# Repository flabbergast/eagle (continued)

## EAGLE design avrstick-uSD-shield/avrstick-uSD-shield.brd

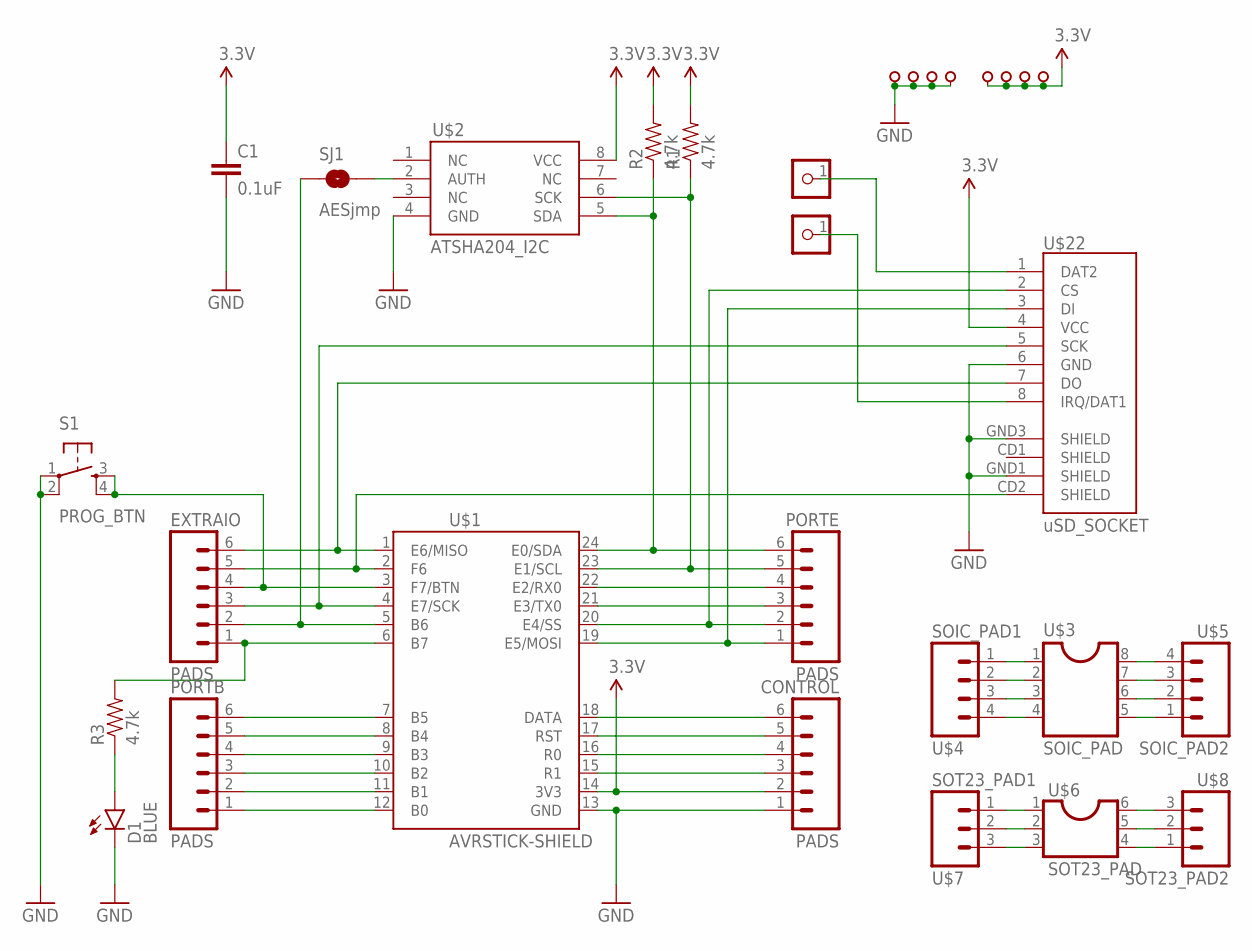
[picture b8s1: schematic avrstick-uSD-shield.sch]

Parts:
C1: 0.1uF; 1206
CONTROL: PADS; M06_SIDESILK_B
D1: BLUE; LED-1206
EXTRAIO: PADS; M06_SIDESILK_T
J1, J2: CON_HEADER_1X01-SMD; SMDPAD05X05
PORTB: PADS; M06_SIDESILK_T
PORTE: PADS; M06_SIDESILK_B
R1, R2, R3: 4.7k; 1206
S1: PROG_BTN; TACTILE-SWITCH-SMD
SJ1: AESjmp; PAD-JUMPER-2-NO_YES_SILK
U$1: AVRSTICK-SHIELD
U$2: ATSHA204_I2C; SOIC-8-NARROW
U$3: SOIC_PAD; SOIC-8-NARROW
U$4: SOIC_PAD1; M04_SILK_1SQ
U$5: SOIC_PAD2; M04_SILK
U$6: SOT23_PAD; SOT23-6
U$7: SOT23_PAD1; M03_SILK_1SQ
U$8: SOT23_PAD2; M03_SILK
U$9, U$10, U$11, U$12, U$13, U$14: M01_SIDESILK
U$15, U$16: M01_NOSILK
U$22: uSD_SOCKET; MICROSD_SOCKET_SPARKFUN

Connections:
3.3V: C1.1, CONTROL.2, R1.2, R2.2, U$1.14 (3V3), U$2.8 (VCC), U$12.1, U$13.1, U$14.1, U$16.1, U$22.4 (VCC)
GND: C1.2, CONTROL.1, D1.C, S1.1, S1.2, U$1.13 (GND), U$2.4 (GND), U$9.1, U$10.1, U$11.1, U$15.1, U$22.6 (GND), U$22.GND1 (SHIELD), U$22.GND3 (SHIELD)
unnamed: EXTRAIO.1, R3.2, U$1.6 (B7)
unnamed: EXTRAIO.2, SJ1.1, U$1.5 (B6)
unnamed: EXTRAIO.3, U$1.4 (E7/SCK), U$22.5 (SCK)
unnamed: PORTB.6, U$1.7 (B5)
unnamed: EXTRAIO.5, U$1.2 (F6), U$22.CD2 (SHIELD)
unnamed: EXTRAIO.6, U$1.1 (E6/MISO), U$22.7 (DO)
unnamed: EXTRAIO.4, S1.3, S1.4, U$1.3 (F7/BTN)
unnamed: PORTB.5, U$1.8 (B4)
unnamed: PORTB.4, U$1.9 (B3)
unnamed: PORTB.3, U$1.10 (B2)
unnamed: PORTB.2, U$1.11 (B1)
unnamed: PORTB.1, U$1.12 (B0)
unnamed: SJ1.2, U$2.2 (AUTH)
unnamed: D1.A, R3.1
unnamed: CONTROL.3, U$1.15 (R1)
unnamed: CONTROL.4, U$1.16 (R0)
unnamed: CONTROL.5, U$1.17 (RST)
unnamed: CONTROL.6, U$1.18 (DATA)
unnamed: PORTE.1, U$1.19 (E5/MOSI), U$22.3 (DI)
unnamed: PORTE.2, U$1.20 (E4/SS), U$22.2 (CS)
unnamed: PORTE.3, U$1.21 (E3/TX0)
unnamed: PORTE.4, U$1.22 (E2/RX0)
unnamed: PORTE.5, R1.1, U$1.23 (E1/SCL), U$2.6 (SCK)
unnamed: PORTE.6, R2.1, U$1.24 (E0/SDA), U$2.5 (SDA)
unnamed: U$3.5, U$5.1
unnamed: U$3.6, U$5.2
unnamed: U$3.7, U$5.3
unnamed: U$3.8, U$5.4
unnamed: U$3.1, U$4.1
unnamed: U$3.2, U$4.2
unnamed: U$3.3, U$4.3
unnamed: U$3.4, U$4.4
unnamed: U$6.4, U$8.1
unnamed: U$6.5, U$8.2
unnamed: U$6.6, U$8.3
unnamed: U$6.1, U$7.1
unnamed: U$6.2, U$7.2
unnamed: U$6.3, U$7.3
unnamed: J2.1, U$22.8 (IRQ/DAT1)
unnamed: J1.1, U$22.1 (DAT2)

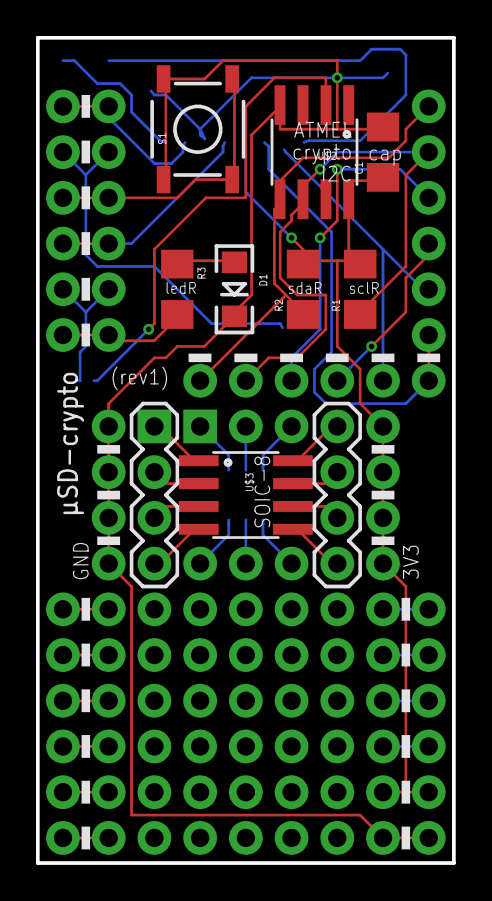
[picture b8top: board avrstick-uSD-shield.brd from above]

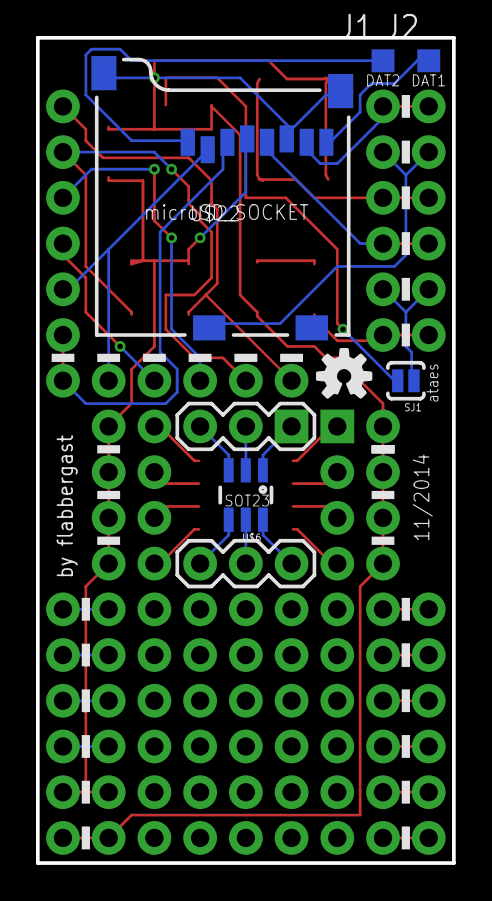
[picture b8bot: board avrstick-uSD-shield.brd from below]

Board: 2 copper layers, 23.1 x 45.8 mm, 36 parts (8 on the bottom side), 42 nets.

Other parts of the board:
U$17, U$18, U$19, U$20, U$21: M06_PROTOPAD; M06_NOSILK
U$23: OSHW-LOGO-S

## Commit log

2014-12-11 Add avrstick-uSD-shield and uext-microSD.
2014-12-17 Add X-A4U rev1 stick.
2015-02-09 Add X-A4U-r2.
2015-02-10 Add png schematic of X-A4U-r2 board.
2015-03-18 Update silk on X-A4U-r2 (2.1).
2015-05-16 Add little2wire and avrisp level translator.
2015-09-11 Add STM32F042FxP6 breakout board.
2015-09-11 Add stm32f042fxp6 breakout png schematic.
2016-01-26 Add KL27Z and STM32F030 breakouts.
2016-01-26 Update README.
2026-04-14 Add bmp.
